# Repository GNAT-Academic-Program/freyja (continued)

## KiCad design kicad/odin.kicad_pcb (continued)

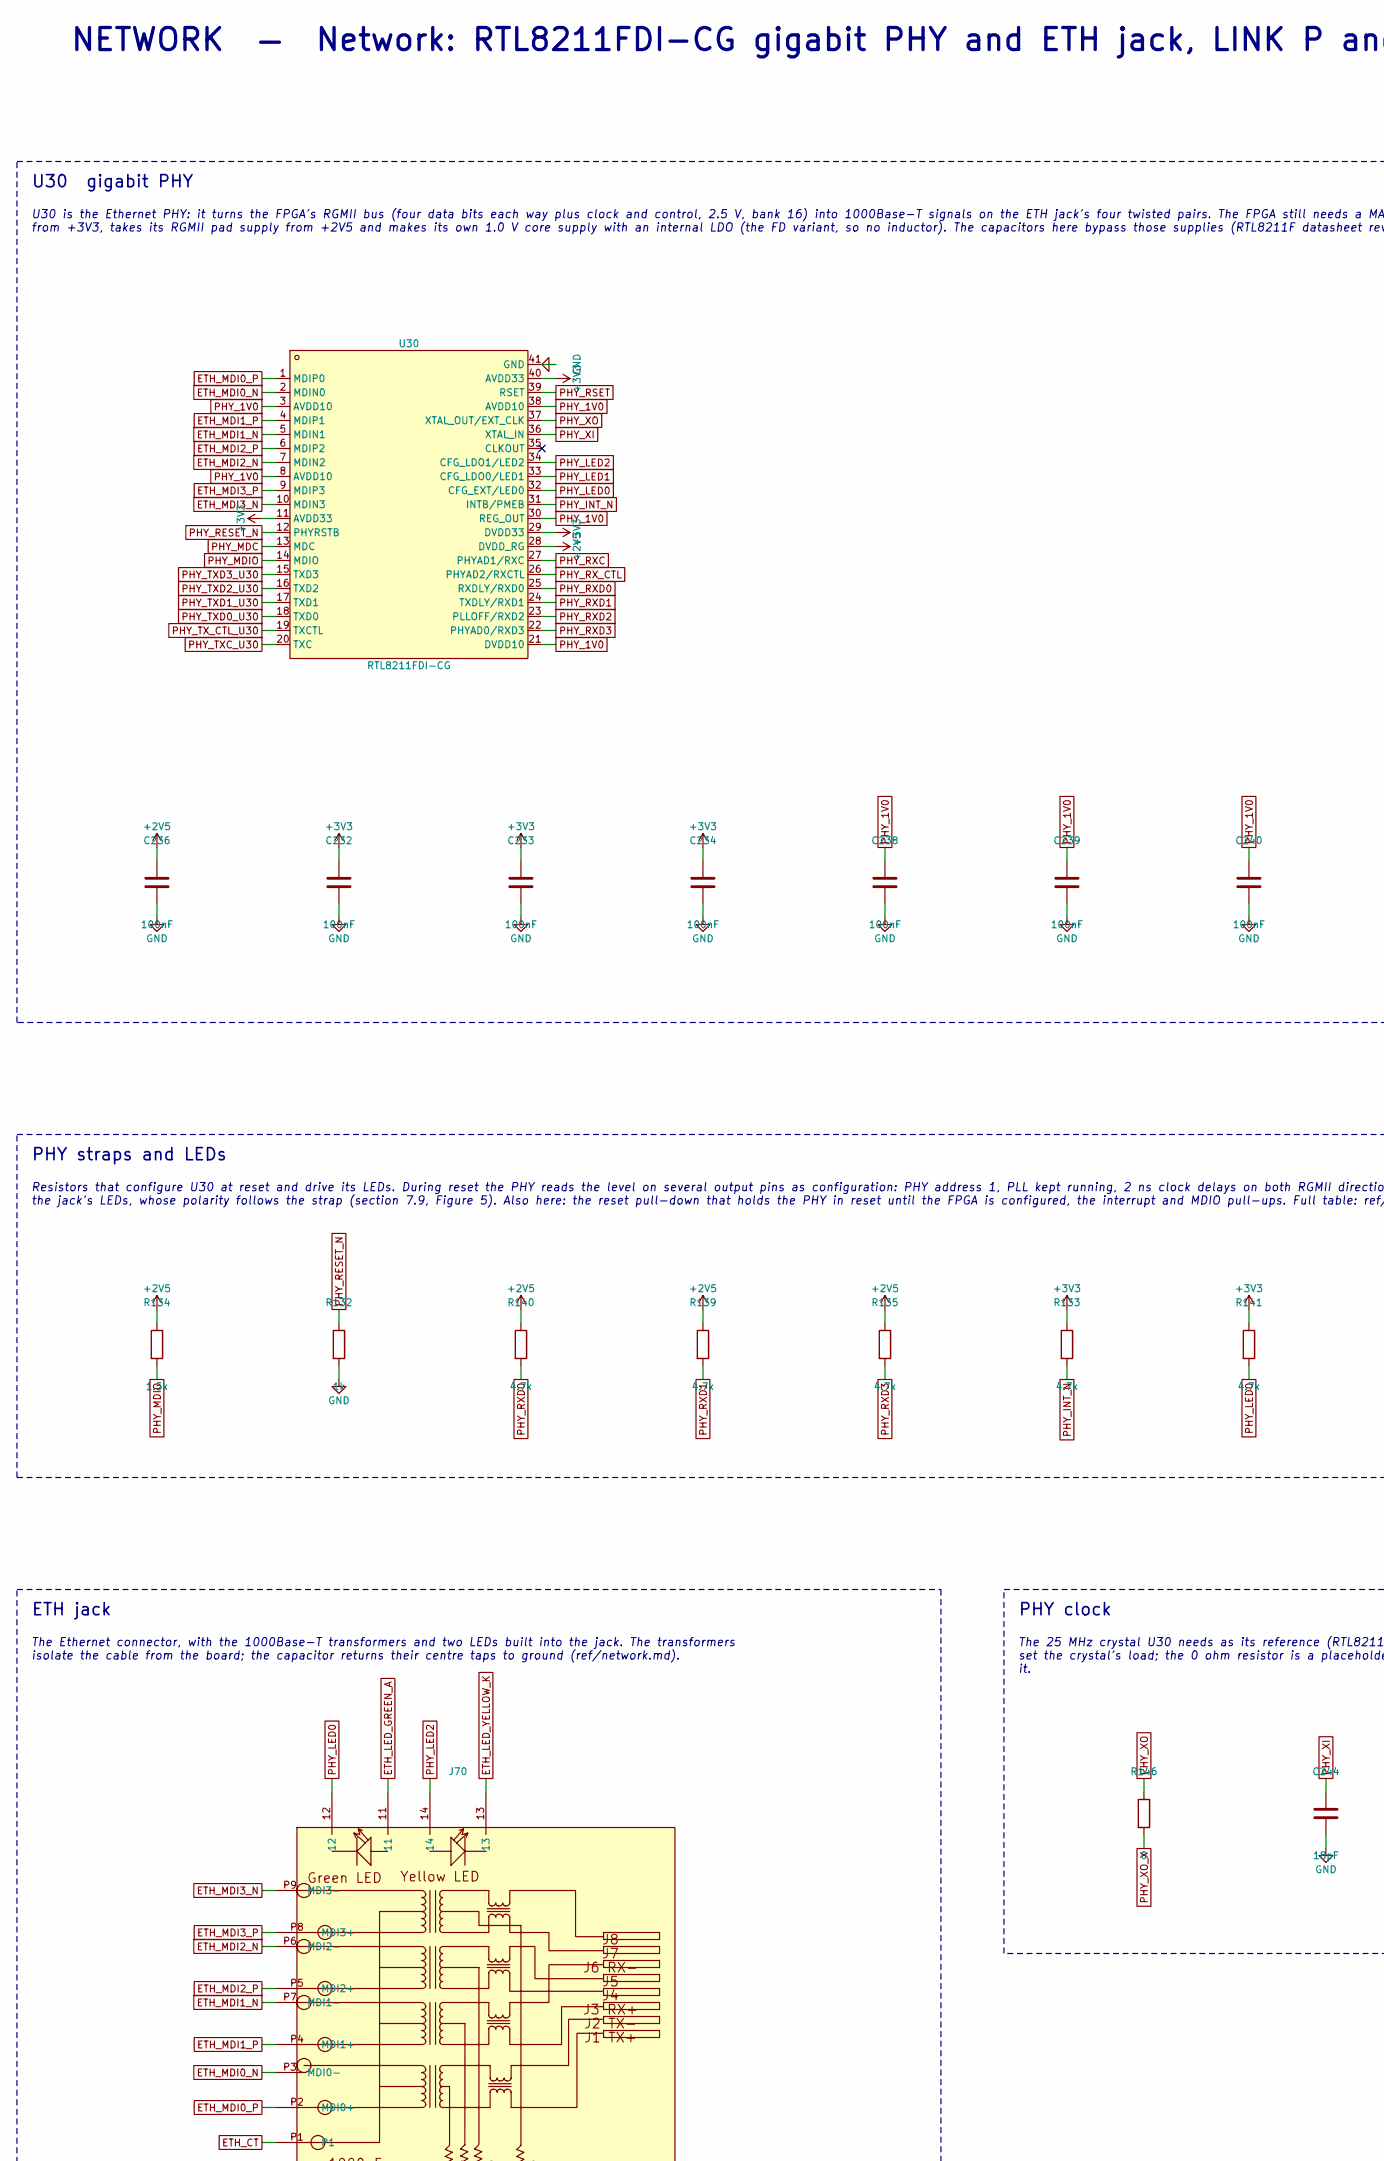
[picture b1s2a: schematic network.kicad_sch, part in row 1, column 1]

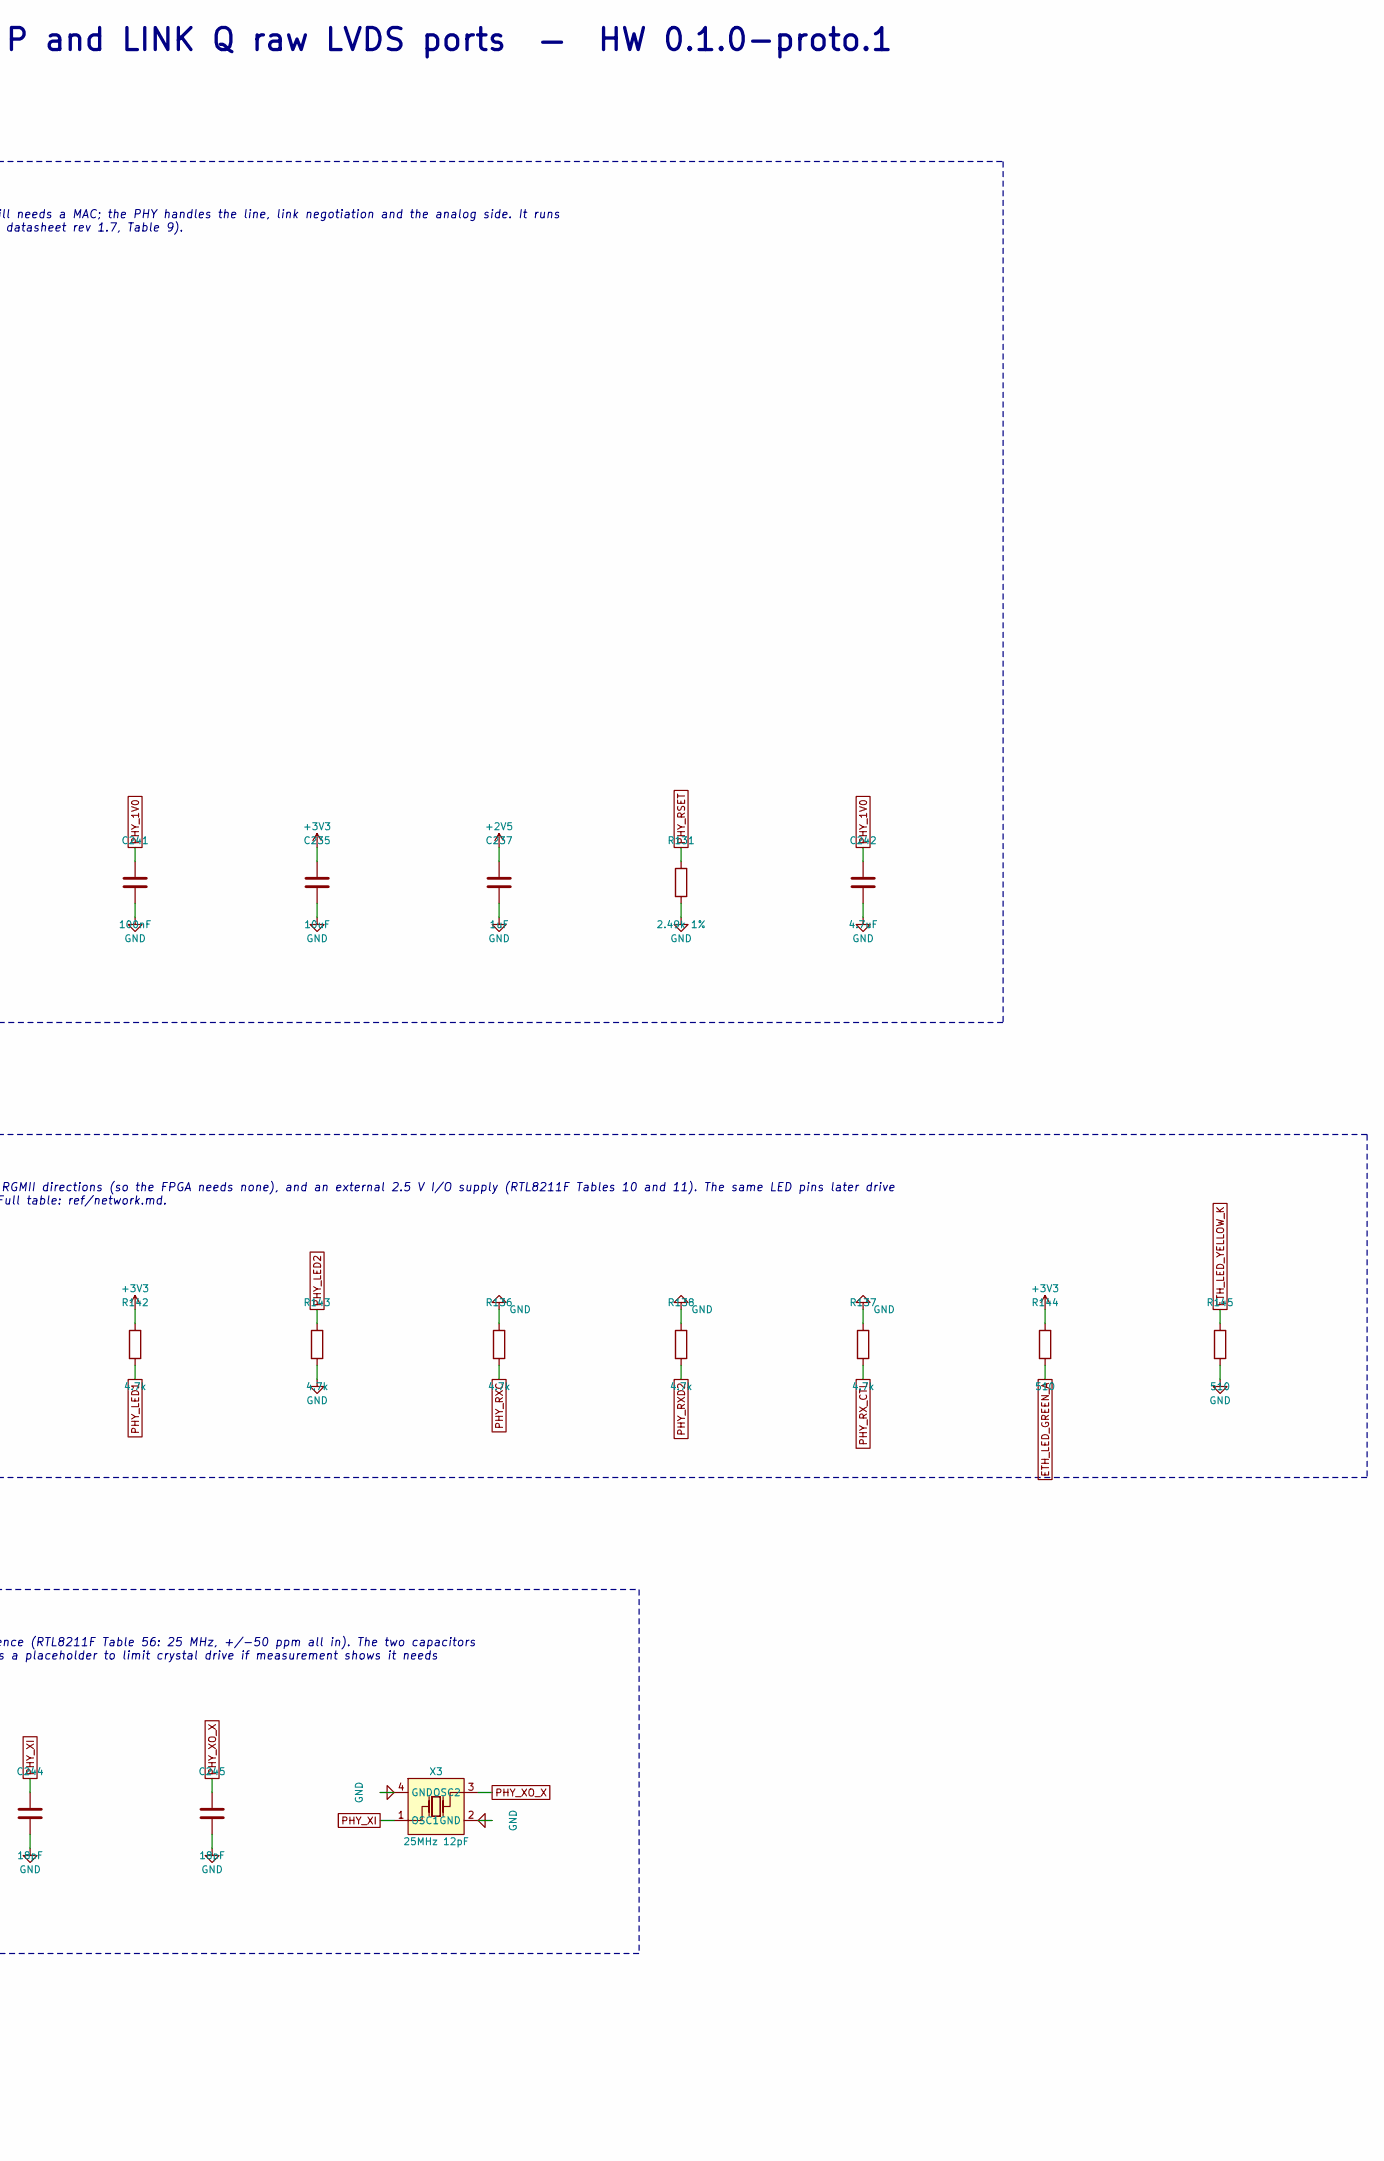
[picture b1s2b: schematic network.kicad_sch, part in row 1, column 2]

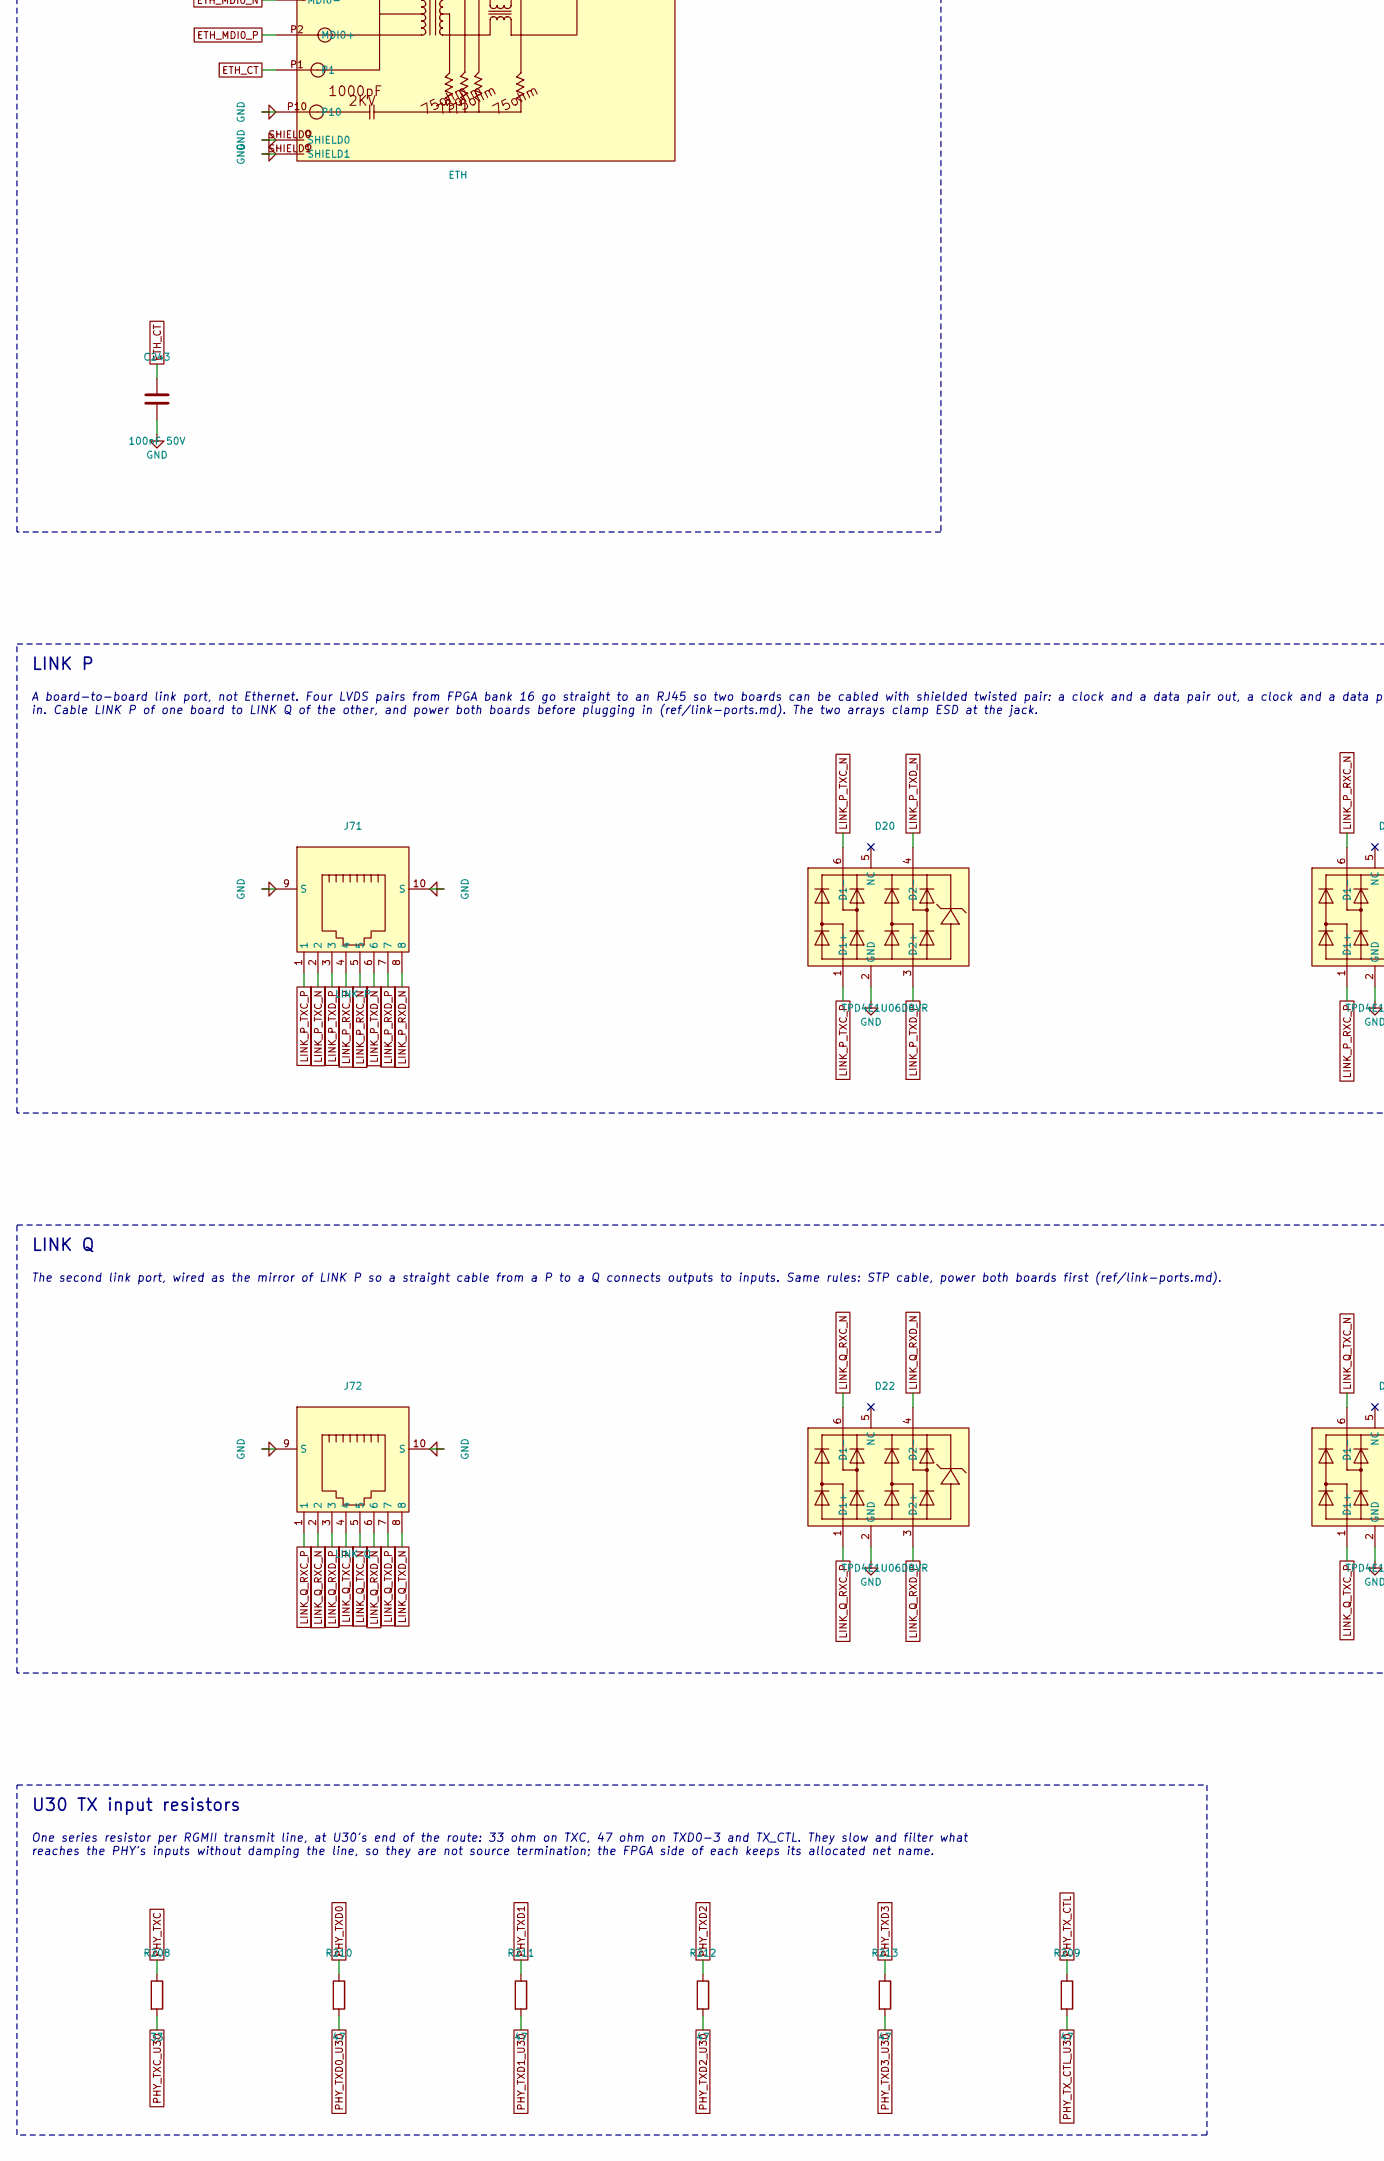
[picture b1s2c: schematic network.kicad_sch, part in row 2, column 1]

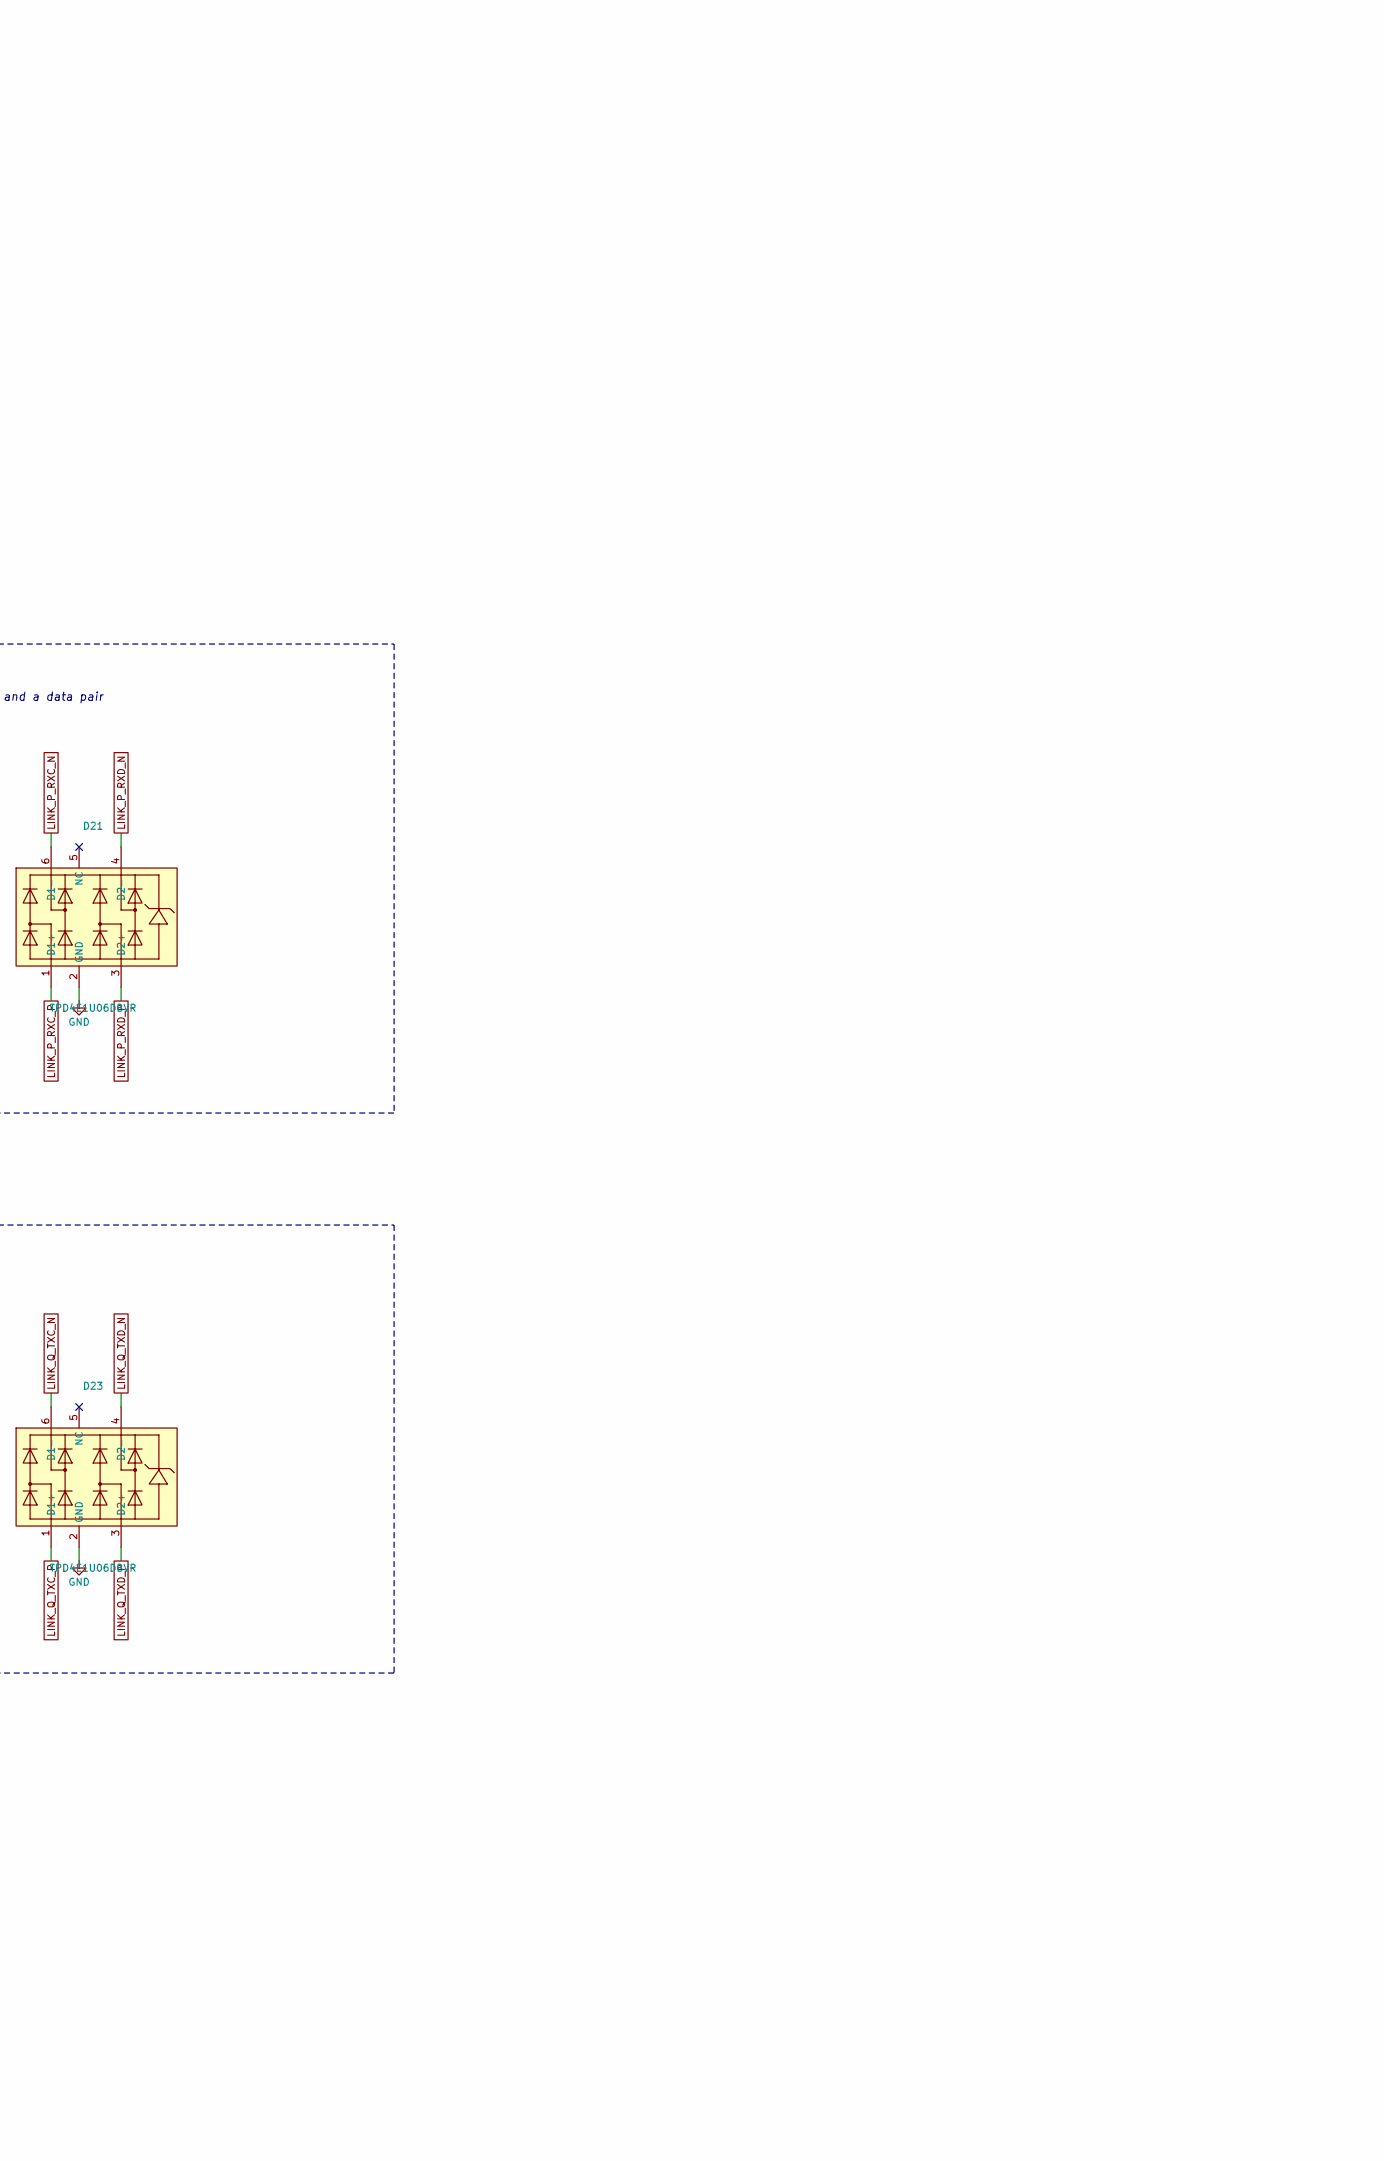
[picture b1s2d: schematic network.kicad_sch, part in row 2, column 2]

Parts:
C232, C233, C234, C236, C238, C239, C240, C241: 100nF; C_0402_1005Metric; LCSC C1525
C235: 10uF; C_0805_2012Metric; LCSC C15850
C237: 1uF; C_0603_1608Metric; LCSC C29936
C242: 4.7uF; C_0603_1608Metric; LCSC C277476
C243: 100nF 50V; C_0603_1608Metric
C244, C245: 18pF; C_0402_1005Metric
D20, D21, D22, D23: TPD4E1U06DBVR; SOT-23-6_L2.9-W1.6-P0.95-LS2.8-BR_TPD4E1U06; LCSC C124691
J70: ETH; RJ45-TH_HR911130A; LCSC C54408
J71: LINK P; RJ45-TH_R-RJ45R08P-B000; LCSC C386756
J72: LINK Q; RJ45-TH_R-RJ45R08P-B000; LCSC C386756
R131: 2.49k 1%; R_0402_1005Metric
R132: 1k; R_0402_1005Metric; LCSC C11702
R133, R135, R136, R137, R138, R139, R140, R141, R142, R143: 4.7k; R_0402_1005Metric; LCSC C25900
R134: 1.5k; R_0402_1005Metric
R144, R145: 510; R_0402_1005Metric
R146: 0; R_0402_1005Metric
R208: 33; R_0402_1005Metric; LCSC C25105
R209, R210, R211, R212, R213: 47; R_0402_1005Metric
U30: RTL8211FDI-CG; QFN-40_L5.0-W5.0-P0.40-BL-EP3.7; LCSC C692886
X3: 25MHz 12pF; CRYSTAL-SMD_4P-L3.2-W2.5-BL_X3225; LCSC C9006

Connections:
+2V5: C236.1, C237.1, R134.1, R135.1, R139.1, R140.1, U30.28 (DVDD_RG); also elsewhere on the board
+3V3: C232.1, C233.1, C234.1, C235.1, R133.1, R141.1, R142.1, R144.1, U30.11 (AVDD33), U30.29 (DVDD33), U30.40 (AVDD33); also elsewhere on the board
ETH_CT: C243.1, J70.P1
ETH_LED_GREEN_A: J70.11, R144.2
ETH_LED_YELLOW_K: J70.13, R145.1
ETH_MDI0_N: J70.P3 (MDI0-), U30.2 (MDIN0)
ETH_MDI0_P: J70.P2 (MDI0+), U30.1 (MDIP0)
ETH_MDI1_N: J70.P7 (MDI1-), U30.5 (MDIN1)
ETH_MDI1_P: J70.P4 (MDI1+), U30.4 (MDIP1)
ETH_MDI2_N: J70.P6 (MDI2-), U30.7 (MDIN2)
ETH_MDI2_P: J70.P5 (MDI2+), U30.6 (MDIP2)
ETH_MDI3_N: J70.P9 (MDI3-), U30.10 (MDIN3)
ETH_MDI3_P: J70.P8 (MDI3+), U30.9 (MDIP3)
GND: C232.2, C233.2, C234.2, C235.2, C236.2, C237.2, C238.2, C239.2, C240.2, C241.2, C242.2, C243.2, C244.2, C245.2, D20.2 (GND), D21.2 (GND), D22.2 (GND), D23.2 (GND), J70.P10, J70.SHIELD0, J70.SHIELD1, J71.9 (S), J71.10 (S), J72.9 (S), J72.10 (S), R131.2, R132.2, R136.1, R137.1, R138.1, R143.2, R145.2, U30.41 (GND), X3.2 (GND), X3.4 (GND); also elsewhere on the board
LINK_P_RXC_N: D21.6 (D1-), J71.5; also elsewhere on the board
LINK_P_RXC_P: D21.1 (D1+), J71.4; also elsewhere on the board
LINK_P_RXD_N: D21.4 (D2-), J71.8; also elsewhere on the board
LINK_P_RXD_P: D21.3 (D2+), J71.7; also elsewhere on the board
LINK_P_TXC_N: D20.6 (D1-), J71.2; also elsewhere on the board
LINK_P_TXC_P: D20.1 (D1+), J71.1; also elsewhere on the board
LINK_P_TXD_N: D20.4 (D2-), J71.6; also elsewhere on the board
LINK_P_TXD_P: D20.3 (D2+), J71.3; also elsewhere on the board
LINK_Q_RXC_N: D22.6 (D1-), J72.2; also elsewhere on the board
LINK_Q_RXC_P: D22.1 (D1+), J72.1; also elsewhere on the board
LINK_Q_RXD_N: D22.4 (D2-), J72.6; also elsewhere on the board
LINK_Q_RXD_P: D22.3 (D2+), J72.3; also elsewhere on the board
LINK_Q_TXC_N: D23.6 (D1-), J72.5; also elsewhere on the board
LINK_Q_TXC_P: D23.1 (D1+), J72.4; also elsewhere on the board
LINK_Q_TXD_N: D23.4 (D2-), J72.8; also elsewhere on the board
LINK_Q_TXD_P: D23.3 (D2+), J72.7; also elsewhere on the board
PHY_1V0: C238.1, C239.1, C240.1, C241.1, C242.1, U30.3 (AVDD10), U30.8 (AVDD10), U30.21 (DVDD10), U30.30 (REG_OUT), U30.38 (AVDD10)
PHY_INT_N: R133.2, U30.31 (INTB/PMEB); also elsewhere on the board
PHY_LED0: J70.12, R141.2, U30.32 (CFG_EXT/LED0)
PHY_LED1: R142.2, U30.33 (CFG_LDO0/LED1)
PHY_LED2: J70.14, R143.1, U30.34 (CFG_LDO1/LED2)
PHY_MDC: U30.13 (MDC); also elsewhere on the board
PHY_MDIO: R134.2, U30.14 (MDIO); also elsewhere on the board
PHY_RESET_N: R132.1, U30.12 (PHYRSTB); also elsewhere on the board
PHY_RSET: R131.1, U30.39 (RSET)
PHY_RXC: R136.2, U30.27 (PHYAD1/RXC); also elsewhere on the board
PHY_RXD0: R140.2, U30.25 (RXDLY/RXD0); also elsewhere on the board
PHY_RXD1: R139.2, U30.24 (TXDLY/RXD1); also elsewhere on the board
PHY_RXD2: R138.2, U30.23 (PLLOFF/RXD2); also elsewhere on the board
PHY_RXD3: R135.2, U30.22 (PHYAD0/RXD3); also elsewhere on the board
PHY_RX_CTL: R137.2, U30.26 (PHYAD2/RXCTL); also elsewhere on the board
PHY_TXC: R208.1; also elsewhere on the board
PHY_TXC_U30: R208.2, U30.20 (TXC)
PHY_TXD0: R210.1; also elsewhere on the board
PHY_TXD0_U30: R210.2, U30.18 (TXD0)
PHY_TXD1: R211.1; also elsewhere on the board
PHY_TXD1_U30: R211.2, U30.17 (TXD1)
PHY_TXD2: R212.1; also elsewhere on the board
PHY_TXD2_U30: R212.2, U30.16 (TXD2)
PHY_TXD3: R213.1; also elsewhere on the board
PHY_TXD3_U30: R213.2, U30.15 (TXD3)
PHY_TX_CTL: R209.1; also elsewhere on the board
PHY_TX_CTL_U30: R209.2, U30.19 (TXCTL)
PHY_XI: C244.1, U30.36 (XTAL_IN), X3.1 (OSC1)
PHY_XO: R146.1, U30.37 (XTAL_OUT/EXT_CLK)
PHY_XO_X: C245.1, R146.2, X3.3 (OSC2)

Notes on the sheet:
NETWORK — Network: RTL8211FDI-CG gigabit PHY and ETH jack, LINK P and LINK Q raw LVDS ports — HW 0.1.0-proto.1
U30 gigabit PHY
U30 is the Ethernet PHY: it turns the FPGA's RGMII bus (four data bits each way plus clock and control, 2.5 V, bank 16) into 1000Base-T signals on the ETH jack's four twisted pairs. The FPGA still needs a MAC; the PHY handles the line, link negotiation and the analog side. It runs from +3V3, takes 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
PHY straps and LEDs
Resistors that configure U30 at reset and drive its LEDs. During reset the PHY reads the level on several output pins as configuration: PHY address 1, PLL kept running, 2 ns clock delays on both RGMII directions (so the FPGA needs none), and an external 2.5 V I/O supply (RTL8211F Tables 10 and 11).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
ETH jack
The Ethernet connector, with the 1000Base-T transformers and two LEDs built into the jack. The transformers isolate the cable from the board; the capacitor returns their centre taps to ground (ref/network.md).
PHY clock
The 25 MHz crystal U30 needs as its reference (RTL8211F Table 56: 25 MHz, +/-50 ppm all in). The two capacitors set the crystal's load; the 0 ohm resistor is a placeholder to limit crystal drive if measurement shows it needs it.
LINK P
A board-to-board link port, not Ethernet. Four LVDS pairs from FPGA bank 16 go straight to an RJ45 so two boards can be cabled with shielded twisted pair: a clock and a data pair out, a clock and a data pair in. Cable LINK P of one board to LINK Q of the other, and power both boards before plugging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
LINK Q
The second link port, wired as the mirror of LINK P so a straight cable from a P to a Q connects outputs to inputs. Same rules: STP cable, power both boards first (ref/link-ports.md).
U30 TX input resistors
One series resistor per RGMII transmit line, at U30's end of the route: 33 ohm on TXC, 47 ohm on TXD0-3 and TX_CTL. They slow and filter what reaches the PHY's inputs without damping the line, so they are not source termination; the FPGA side of each keeps its allocated net name.

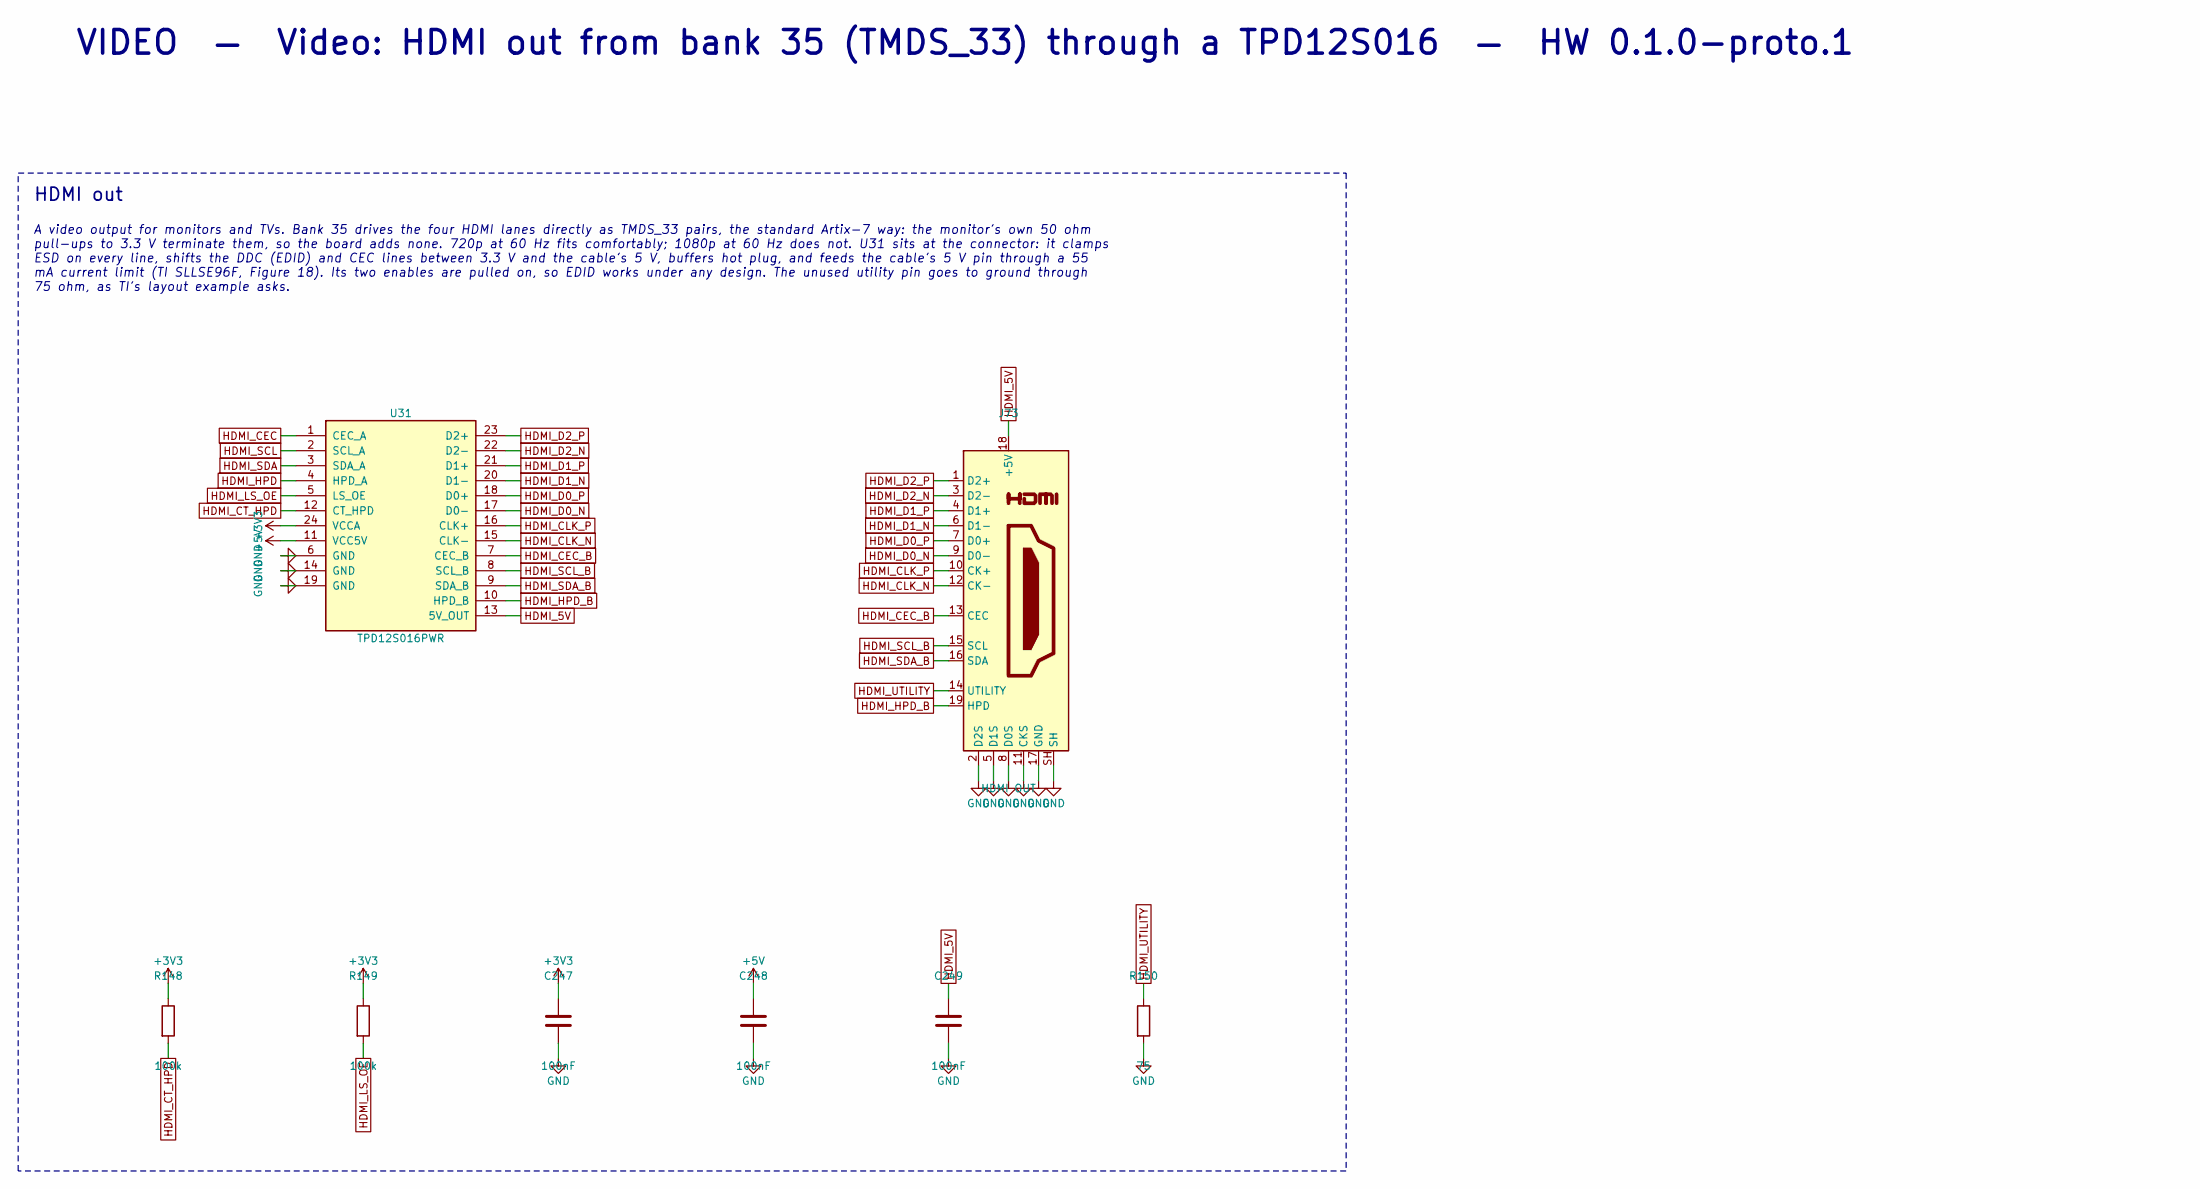
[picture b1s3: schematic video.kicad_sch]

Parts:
C247, C248, C249: 100nF; C_0402_1005Metric; LCSC C1525
J73: HDMI OUT; HDMI_A_Amphenol_10029449-x01xLF_Horizontal; LCSC C427307
R148, R149: 100k; R_0402_1005Metric; LCSC C25741
R150: 75; R_0402_1005Metric
U31: TPD12S016PWR; TSSOP-24_4.4x7.8mm_P0.65mm; LCSC C201665

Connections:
+3V3: C247.1, R148.1, R149.1, U31.24 (VCCA); also elsewhere on the board
+5V: C248.1, U31.11 (VCC5V); also elsewhere on the board
GND: C247.2, C248.2, C249.2, J73.2 (D2S), J73.5 (D1S), J73.8 (D0S), J73.11 (CKS), J73.17 (GND), J73.SH, R150.2, U31.6 (GND), U31.14 (GND), U31.19 (GND); also elsewhere on the board
HDMI_5V: C249.1, J73.18 (+5V), U31.13 (5V_OUT)
HDMI_CEC: U31.1 (CEC_A); also elsewhere on the board
HDMI_CEC_B: J73.13 (CEC), U31.7 (CEC_B)
HDMI_CLK_N: J73.12 (CK-), U31.15 (CLK-); also elsewhere on the board
HDMI_CLK_P: J73.10 (CK+), U31.16 (CLK+); also elsewhere on the board
HDMI_CT_HPD: R148.2, U31.12 (CT_HPD); also elsewhere on the board
HDMI_D0_N: J73.9 (D0-), U31.17 (D0-); also elsewhere on the board
HDMI_D0_P: J73.7 (D0+), U31.18 (D0+); also elsewhere on the board
HDMI_D1_N: J73.6 (D1-), U31.20 (D1-); also elsewhere on the board
HDMI_D1_P: J73.4 (D1+), U31.21 (D1+); also elsewhere on the board
HDMI_D2_N: J73.3 (D2-), U31.22 (D2-); also elsewhere on the board
HDMI_D2_P: J73.1 (D2+), U31.23 (D2+); also elsewhere on the board
HDMI_HPD: U31.4 (HPD_A); also elsewhere on the board
HDMI_HPD_B: J73.19 (HPD), U31.10 (HPD_B)
HDMI_LS_OE: R149.2, U31.5 (LS_OE); also elsewhere on the board
HDMI_SCL: U31.2 (SCL_A); also elsewhere on the board
HDMI_SCL_B: J73.15 (SCL), U31.8 (SCL_B)
HDMI_SDA: U31.3 (SDA_A); also elsewhere on the board
HDMI_SDA_B: J73.16 (SDA), U31.9 (SDA_B)
HDMI_UTILITY: J73.14 (UTILITY), R150.1

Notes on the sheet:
VIDEO — Video: HDMI out from bank 35 (TMDS_33) through a TPD12S016 — HW 0.1.0-proto.1
HDMI out
A video output for monitors and TVs. Bank 35 drives the four HDMI lanes directly as TMDS_33 pairs, the standard Artix-7 way: the monitor's own 50 ohm pull-ups to 3.3 V terminate them, so the board adds none. 720p at 60 Hz fits comfortably; 1080p at 60 Hz does not. U31 sits at the connector: it clam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
